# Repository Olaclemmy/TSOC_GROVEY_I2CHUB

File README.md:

# TSOC_GROVEY_I2CHUB
**TSOC_GROVEY_I2CHUB** is a four(4) port I2C Hub/Switch board, an Embedded Module for thingSoC.

The **TSOC_GROVEY_I2CHUB** can operate at either 3.3V or 5V, and can also level translate 3.3V processor I2C bus to 5V peripherals when needed.

The **TSOC_GROVEY_I2CHUB** allows you to connect [thingSoC](http://thingsoc.github.io/), [Mikrobus](http://www.mikroe.com/mikrobus/), 
and/or [Grove System](http://www.seeedstudio.com/blog/2016/03/09/tutorial-intro-to-grove-connectors-for-arduinoraspberry-pi-projects/) 
Modules all at the same time, with any processor module.
This gives you maximum flexiblity for sensor and actuator selection, and reuse. 

The thingSoC "Grovey Series" was designed as "Everyday Electronics", a no-frills, low cost, approach to modular embedded product design.
thingSoC boards are similar in size to most break-out-boards (BOBs), but feature a standardized stacking pinout, as well as an I2C metadata store (EEPROM)
to indicate what peripherals are installed.

[TSOC_GROVEY_I2CHUB](https://github.com/thingSoC/TSOC_GROVEY_I2CHUB/)

---------------------------------------

In this example, we use the [Grovey_I2CHUB](https://github.com/thingSoC/TSOC_GROVEY_I2CHUB) with the [Teensy3.x](https://www.pjrc.com/teensy/index.html) to support a Grove 16x2 LCD panel.
Since the Grove 16x2 LCD panel is a 5V peripheral, the [Grovey_I2CHUB](https://github.com/thingSoC/TSOC_GROVEY_I2CHUB) performs the voltage level translation
necessary to go from the 3.3V micro-processor to the 5V LCD controller. 

[TSOC_GROVEY_I2CHUB](https://github.com/thingSoC/TSOC_GROVEY_I2CHUB/)

* [thingSoC Compliant Module](http://www.thingsoc.com)
* [Mikrobus Compatible Module](http://www.mikroe.com/mikrobus/) 
* 5V Nominal Power Input
* 5V or 3.3V Operation
* Supports four (4) separate I2C busses 

---------------------------------------
## Example Uses

* Any time you want to connect four (4) of the same sensor, using the same I2C address, then you need an I2C Hub/Switch.
* Adds four (4) I2C ports to any [thingSoC](http://thingsoc.github.io/), [Mikrobus](http://www.mikroe.com/mikrobus/), 
and/or [Grove System](http://www.seeedstudio.com/blog/2016/03/09/tutorial-intro-to-grove-connectors-for-arduinoraspberry-pi-projects/) peripherals.

---------------------------------------
## 3D Model (Sketchup)

---------------------------------------
## Project Status

* 09/02/2016 : Revision 2.0 Release for PCB fab

## Revision 2.0 Notes: ##

* Add Ground Strap, remove FM24V10 FRAM, add GROVE I2C Slave connector slot.

## Revision 2.1 Notes: ##

* Remove Ground Strap, it was confusing for power configuration and assembly.
* Prototype testing complete, Production Ready

---------------------------------------

## Documentation Index <a name="documentation_index"/>

[Quick Start Guide](https://github.com/thingSoC/TSOC_GROVEY_I2CHUB/blob/master/TSOC_GROVEY_I2CHUB/docs/QuickStart.md)

[User Guide](https://github.com/thingSoC/TSOC_GROVEY_I2CHUB/blob/master/TSOC_GROVEY_I2CHUB/docs/UserGuide.md)

[Theory of Operation](https://github.com/thingSoC/TSOC_GROVEY_I2CHUB/blob/master/TSOC_GROVEY_I2CHUB/docs/TheoryOfOperation.md)

[thingSoC Organization Website](http://thingSoC.github.io)

[thingSoC FAQ - Frequently Asked Questions](http://thingsoc.github.io/support/faq.html)

---------------------------------------

[  
*thingSoC*](http://thingsoc.github.io)

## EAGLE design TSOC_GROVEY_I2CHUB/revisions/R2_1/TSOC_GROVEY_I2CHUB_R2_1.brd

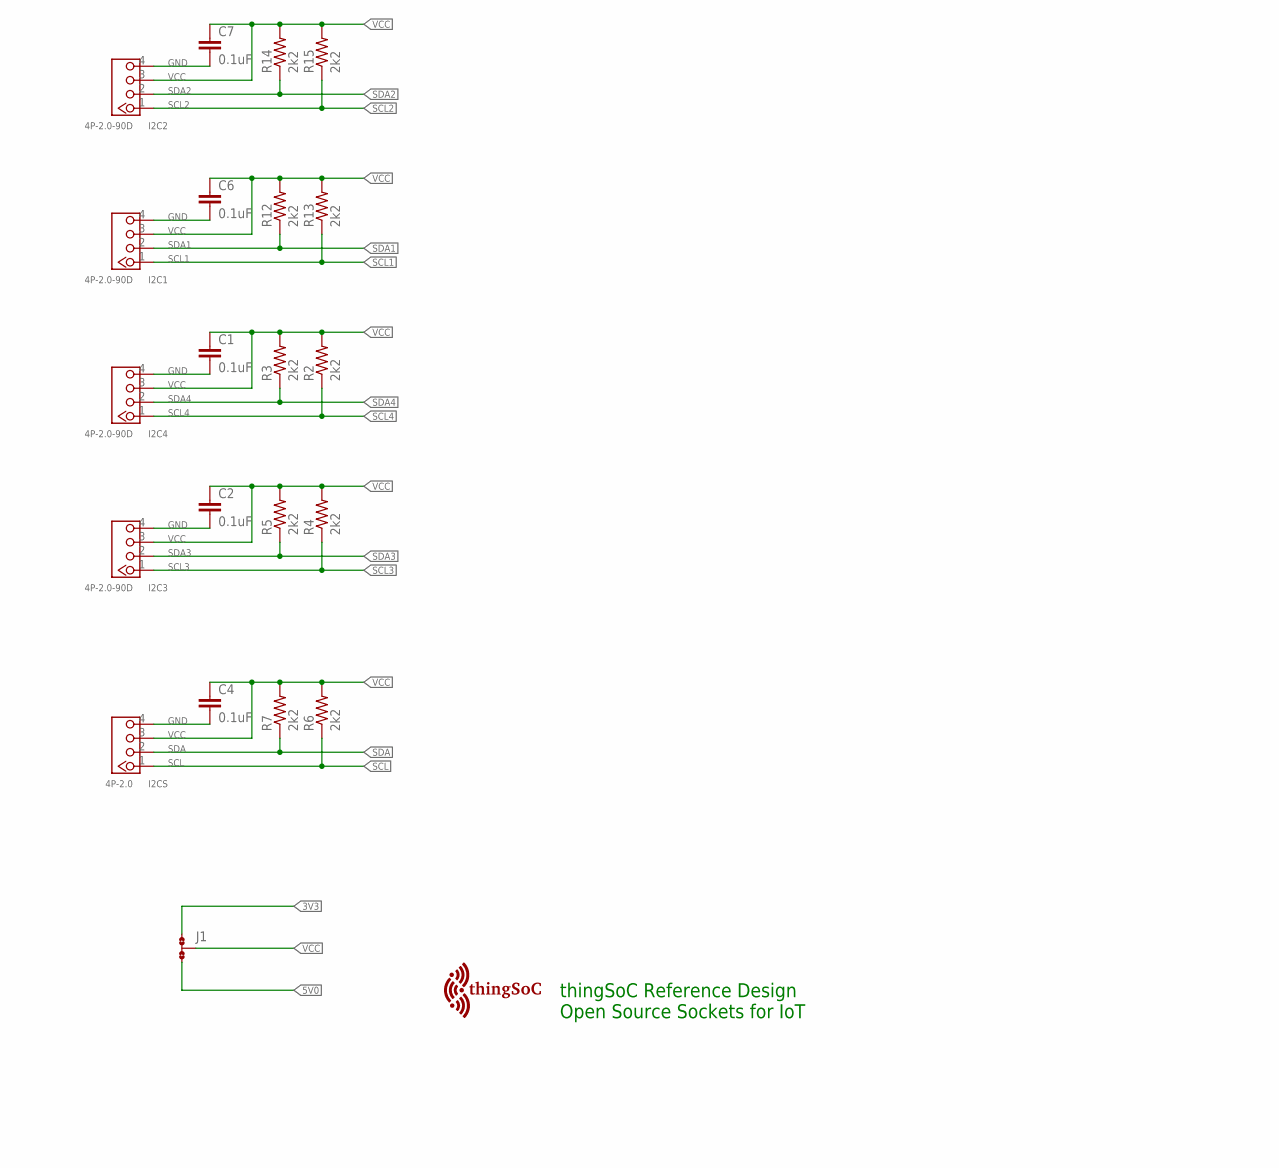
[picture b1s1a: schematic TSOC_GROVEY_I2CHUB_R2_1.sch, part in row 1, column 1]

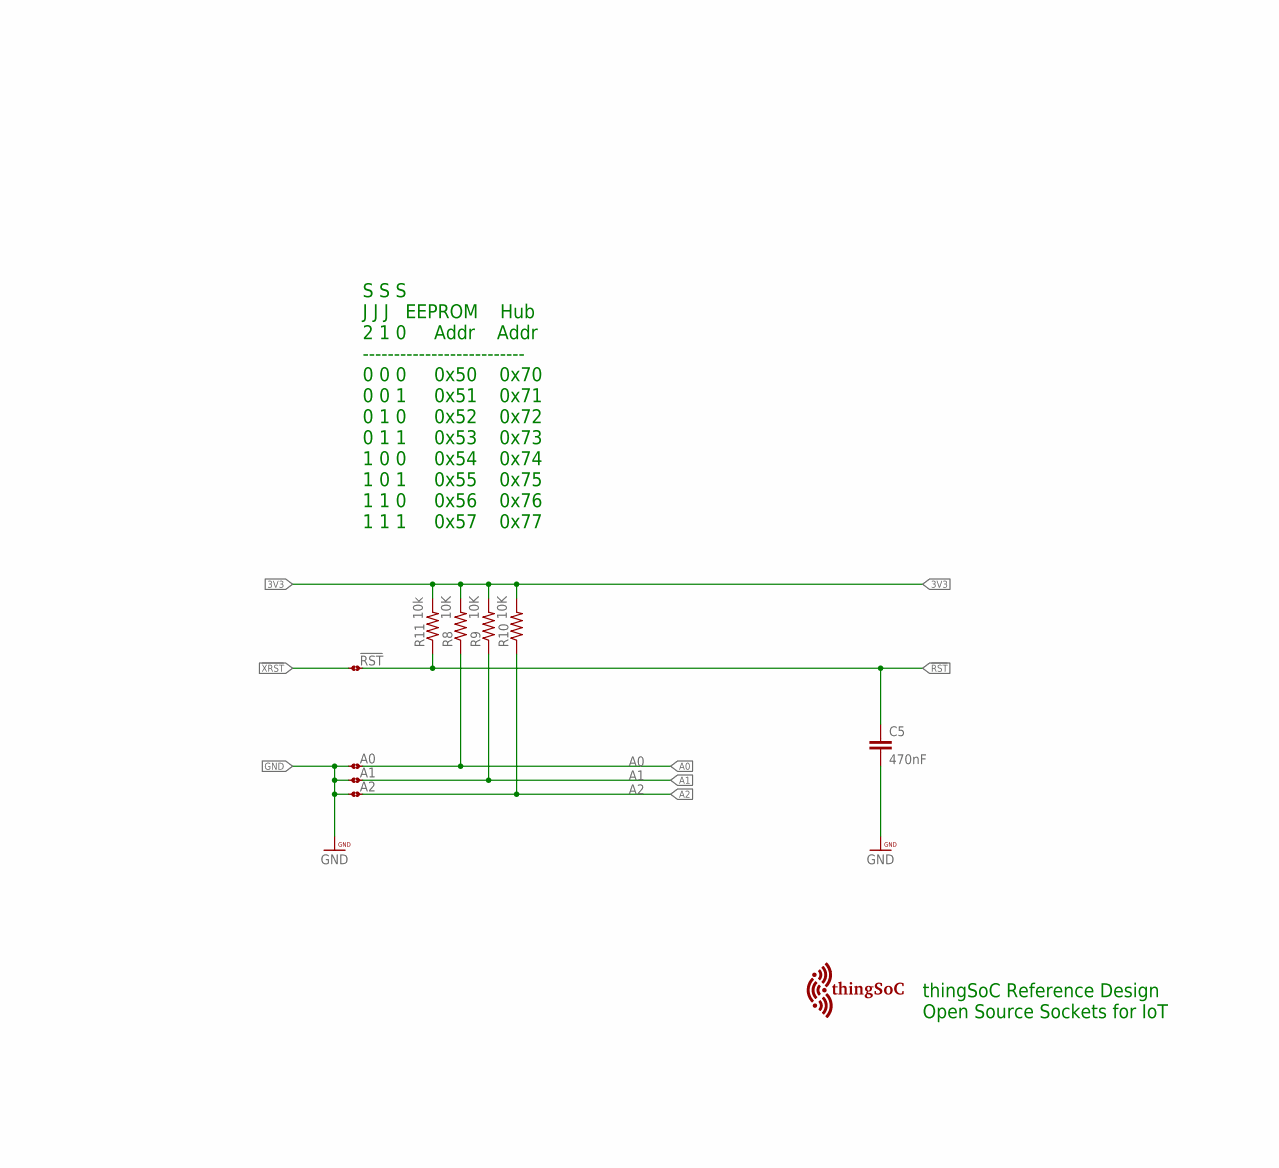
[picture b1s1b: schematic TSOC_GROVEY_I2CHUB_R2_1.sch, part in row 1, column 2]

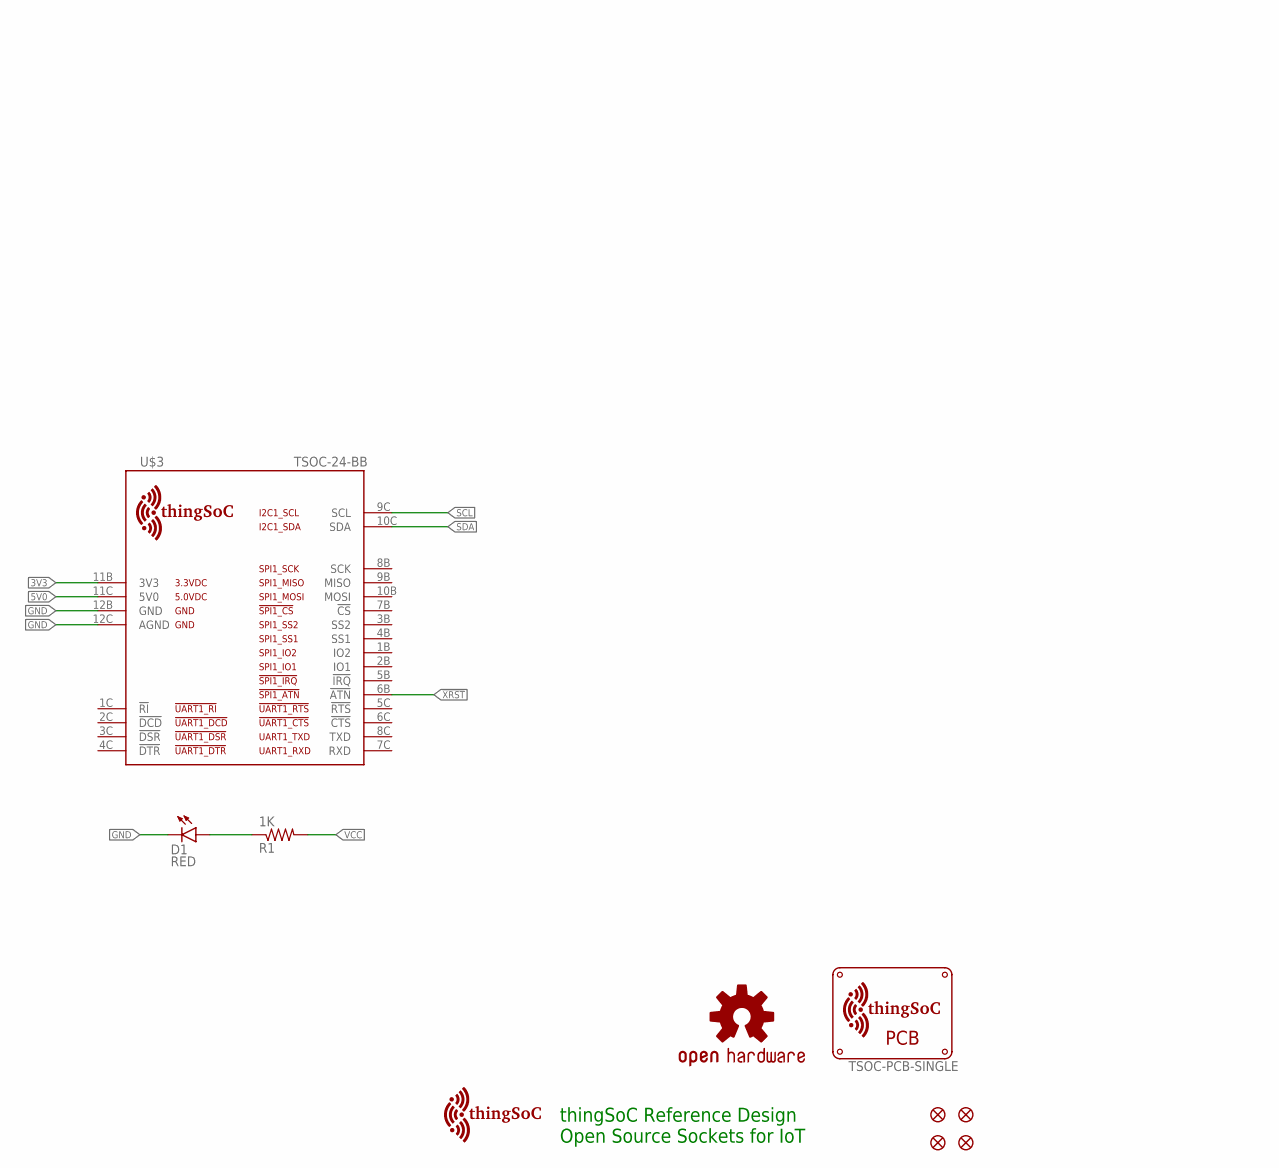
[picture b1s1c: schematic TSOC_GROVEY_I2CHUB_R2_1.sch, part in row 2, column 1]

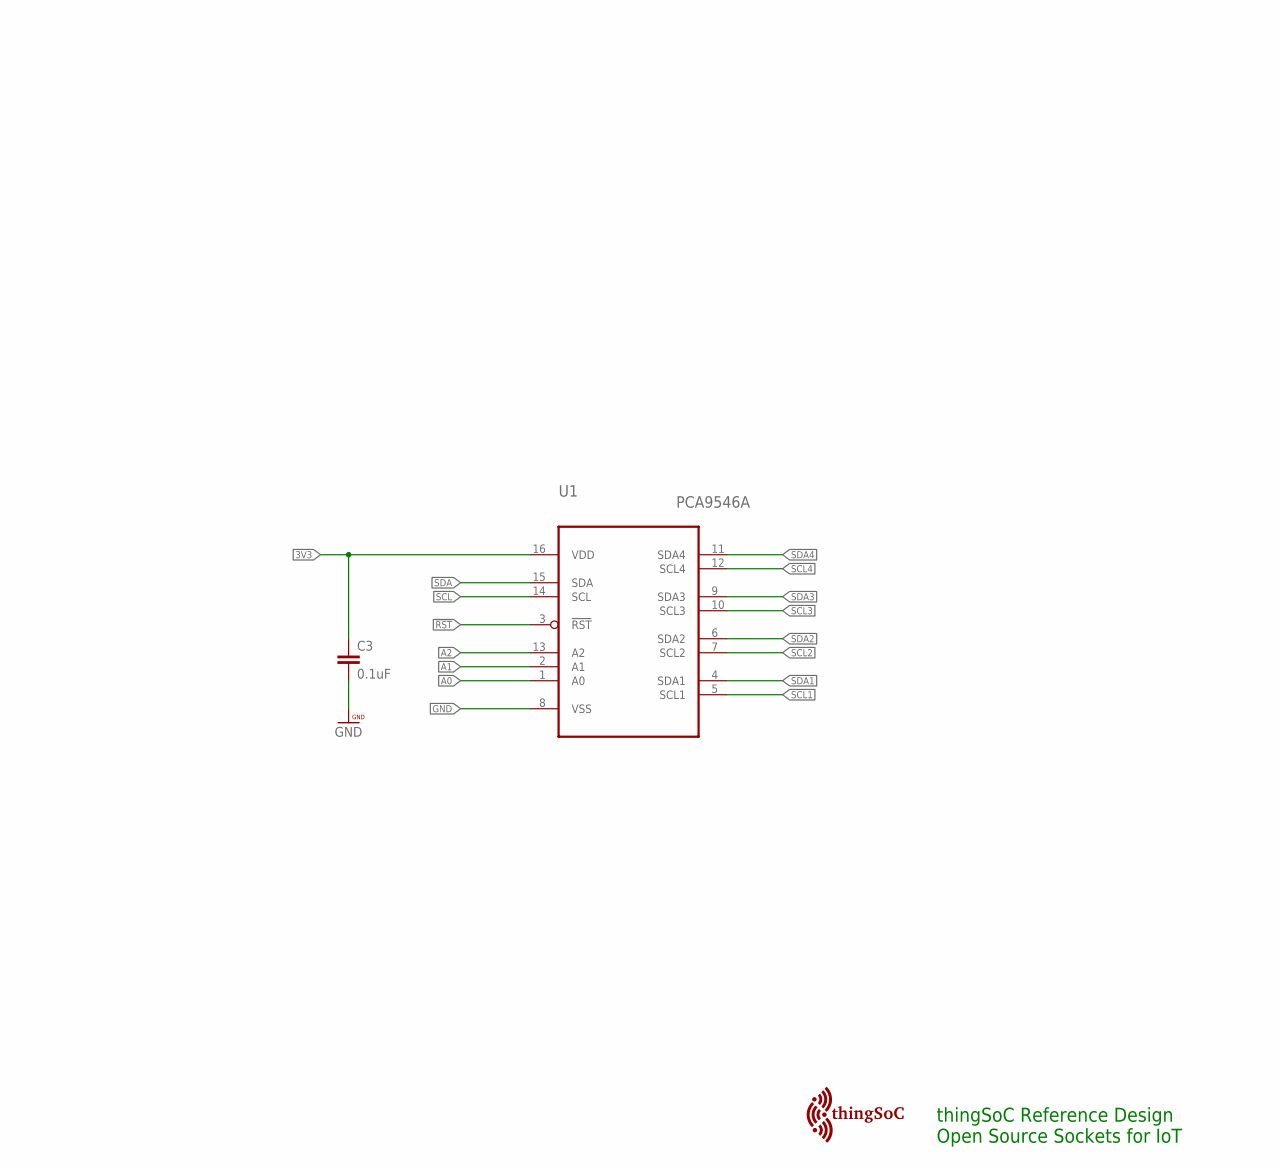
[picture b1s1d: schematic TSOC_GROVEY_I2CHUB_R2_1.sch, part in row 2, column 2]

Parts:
!RST: NO; JMP-2-NO
A0, A1, A2: NO; JMP-2-NO
C1, C2, C3, C4, C6, C7: 0.1uF; 0603-CAP
C5: 470nF; 0603-CAP
D1: RED; LED-0603
FID1, FID2, FID3, FID4: FIDUCIALUFIDUCIAL; MICRO-FIDUCIAL
I2C1, I2C2, I2C3, I2C4: 4P-2.0-90D; HW4-2.0-90D
I2CS: 4P-2.0; HW4-2.0
J1: NO; JMP-3-NO-PTH-2.54
LOGO1: OSHW-LOGOL; OSHW-LOGO-L
R1: 1K; 0603-RES
R2, R3, R4, R5, R6, R7, R12, R13, R14, R15: 2k2; 0603-RES
R8, R9, R10: 10K; 0603-RES
R11: 10k; 0603-RES
U1: PCA9546A; SOP65P640X110-16N
U$1, U$102, U$103: TSOC-LOGO-SMALL; TSOC-LOGO-SML
U$2: TSOC-PCB-SINGLE; TSOC-BB-BRD-DIM
U$3: TSOC-24-BB; TSOC-BB-S24
U$101: TSOC-LOGO-LRG

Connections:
3V3: C3.1, J1.1, R8.2, R9.2, R10.2, R11.2, U1.16 (VDD), U$3.11B (3V3)
5V0: J1.3, U$3.11C (5V0)
!RST: !RST.1, C5.1, R11.1, U1.3 (!RST)
!XRST: !RST.2, U$3.6B (!ATN)
A0: A0.2, R8.1, U1.1 (A0)
A1: A1.2, R9.1, U1.2 (A1)
A2: A2.2, R10.1, U1.13 (A2)
GND: A0.1, A1.1, A2.1, C1.2, C2.2, C3.2, C4.2, C5.2, C6.2, C7.2, D1.C, I2C1.4, I2C2.4, I2C3.4, I2C4.4, I2CS.4, U1.8 (VSS), U$3.12B (GND), U$3.12C (AGND)
unnamed: D1.A, R1.1
SCL: I2CS.1, R6.1, U1.14 (SCL), U$3.9C (SCL)
SCL1: I2C1.1, R13.1, U1.5 (SCL1)
SCL2: I2C2.1, R15.1, U1.7 (SCL2)
SCL3: I2C3.1, R4.1, U1.10 (SCL3)
SCL4: I2C4.1, R2.1, U1.12 (SCL4)
SDA: I2CS.2, R7.1, U1.15 (SDA), U$3.10C (SDA)
SDA1: I2C1.2, R12.1, U1.4 (SDA1)
SDA2: I2C2.2, R14.1, U1.6 (SDA2)
SDA3: I2C3.2, R5.1, U1.9 (SDA3)
SDA4: I2C4.2, R3.1, U1.11 (SDA4)
VCC: C1.1, C2.1, C4.1, C6.1, C7.1, I2C1.3, I2C2.3, I2C3.3, I2C4.3, I2CS.3, J1.2, R1.2, R2.2, R3.2, R4.2, R5.2, R6.2, R7.2, R12.2, R13.2, R14.2, R15.2

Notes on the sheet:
S S S J J J EEPROM Hub 2 1 0 Addr Addr -------------------------- 0 0 0 0x50 0x70 0 0 1 0x51 0x71 0 1 0 0x52 0x72 0 1 1 0x53 0x73 1 0 0 0x54 0x74 1 0 1 0x55 0x75 1 1 0 0x56 0x76 1 1 1 0x57 0x77
thingSoC Reference Design Open Source Sockets for IoT

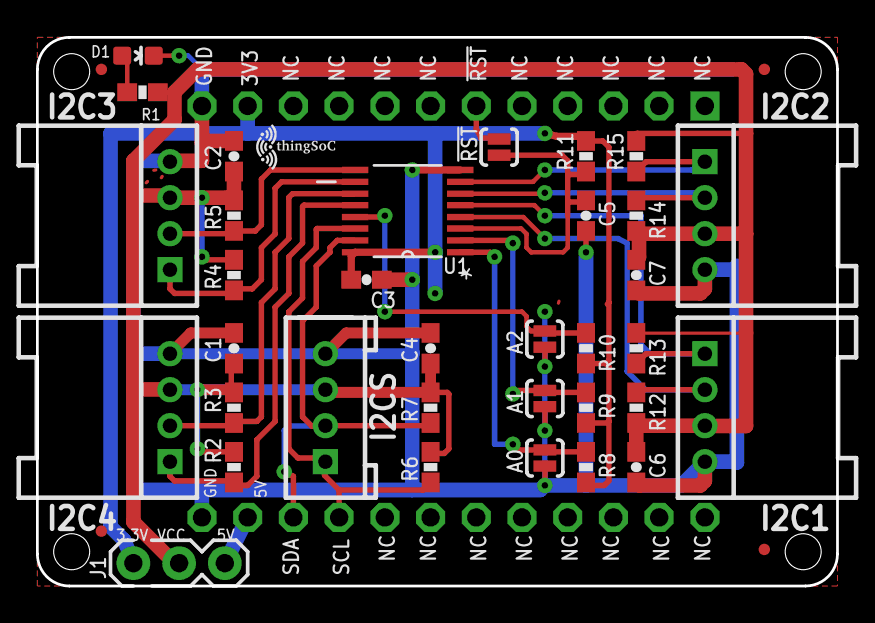
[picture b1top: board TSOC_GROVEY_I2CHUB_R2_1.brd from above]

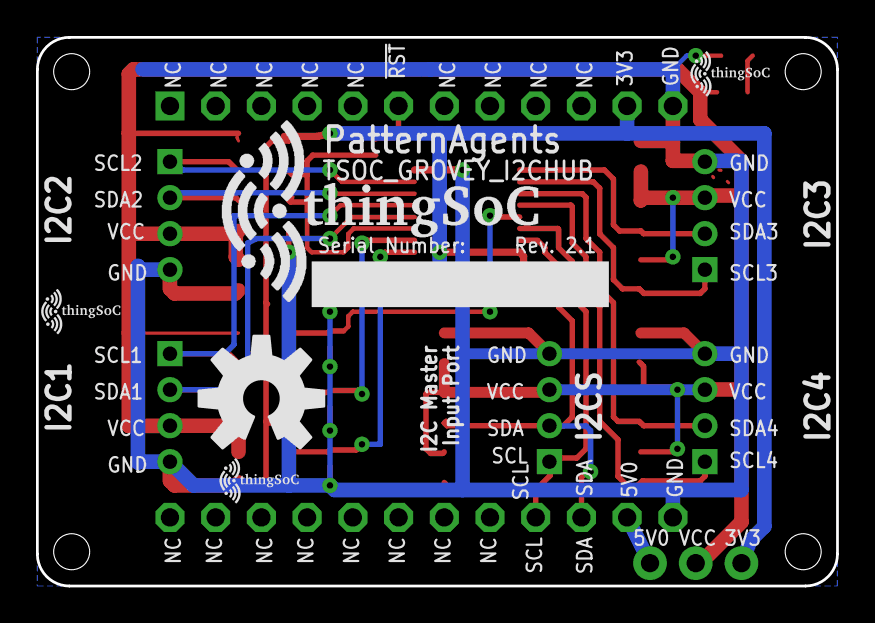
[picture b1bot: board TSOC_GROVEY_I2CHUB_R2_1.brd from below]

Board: 2 copper layers, 44.5 x 30.5 mm, 46 parts (5 on the bottom side), 20 nets.

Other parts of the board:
U$100: TSOC-LOGO-SMALL; TSOC-LOGO-SML

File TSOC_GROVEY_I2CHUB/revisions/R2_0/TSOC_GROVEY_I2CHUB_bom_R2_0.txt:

Partlist exported from U:/PatternAgents/eagle/TSOC_Modules/TSOC_GROVEY_I2CHUB/TSOC_GROVEY_I2CHUB/TSOC_GROVEY_I2CHUB.sch Revison 2.0 at 9/2/2016 12:30:56 PM

Part  Value             Device                          Package           Description                           
D1    RED               LED0603                         LED-0603          LEDs                                  
C1    0.1uF             CAP0603-CAP                     0603-CAP          Capacitor                             
C2    0.1uF             CAP0603-CAP                     0603-CAP          Capacitor                             
C3    0.1uF             CAP0603-CAP                     0603-CAP          Capacitor                             
C4    0.1uF             CAP0603-CAP                     0603-CAP          Capacitor                             
C5    470pF             CAP0603-CAP                     0603-CAP          Capacitor                             
C6    0.1uF             CAP0603-CAP                     0603-CAP          Capacitor                             
C7    0.1uF             CAP0603-CAP                     0603-CAP          Capacitor                             
I2C1  4P-2.0-90D        GROVE-CONNECTOR-DIP-90D(4P-2.0) HW4-2.0-90D       320110034                             
I2C2  4P-2.0-90D        GROVE-CONNECTOR-DIP-90D(4P-2.0) HW4-2.0-90D       320110034                             
I2C3  4P-2.0-90D        GROVE-CONNECTOR-DIP-90D(4P-2.0) HW4-2.0-90D       320110034                             
I2C4  4P-2.0-90D        GROVE-CONNECTOR-DIP-90D(4P-2.0) HW4-2.0-90D       320110034                             
R1    1K                RESISTOR_SFE0603-RES            0603-RES          Resistor                              
R2    2k2               RESISTOR0603-RES                0603-RES          Resistor                              
R3    2k2               RESISTOR0603-RES                0603-RES          Resistor                              
R4    2k2               RESISTOR0603-RES                0603-RES          Resistor                              
R5    2k2               RESISTOR0603-RES                0603-RES          Resistor                              
R6    2k2               RESISTOR0603-RES                0603-RES          Resistor                              
R7    2k2               RESISTOR0603-RES                0603-RES          Resistor                              
R8    10K               RESISTOR0603-RES                0603-RES          Resistor                              
R9    10K               RESISTOR0603-RES                0603-RES          Resistor                              
R10   10K               RESISTOR0603-RES                0603-RES          Resistor                              
R11   10k               RESISTOR0603-RES                0603-RES          Resistor                              
R12   2k2               RESISTOR0603-RES                0603-RES          Resistor                              
R13   2k2               RESISTOR0603-RES                0603-RES          Resistor                              
R14   2k2               RESISTOR0603-RES                0603-RES          Resistor                              
R15   2k2               RESISTOR0603-RES                0603-RES          Resistor                              
U1    PCA9546A          PCA9546A                        SOP65P640X110-16N 4-channel I2C-bus switch with reset   
J1    NO                JMP-3-NO-PTH                    JMP-3-NO-PTH-2.54 Three Terminal Jumper
JMP1  Jumper            2 Pin Jumper                    2 Pin Jumper      Installed on J1-1 to J1-2 (3.3V)

Do Not Populate
--------------------------------------------------------------------------------------------
GND                     M01PTH                          1X01              Ground Strap  
I2CS  4P-2.0            GROVE-CONNECTOR-DIP(4P-2.0)     HW4-2.0           320110033                             
!RST  NO                JMP-2-NO                        JMP-2-NO          Basic Jumper - Normally Open          
A0    NO                JMP-2-NO                        JMP-2-NO          Basic Jumper - Normally Open          
A1    NO                JMP-2-NO                        JMP-2-NO          Basic Jumper - Normally Open          
A2    NO                JMP-2-NO                        JMP-2-NO          Basic Jumper - Normally Open

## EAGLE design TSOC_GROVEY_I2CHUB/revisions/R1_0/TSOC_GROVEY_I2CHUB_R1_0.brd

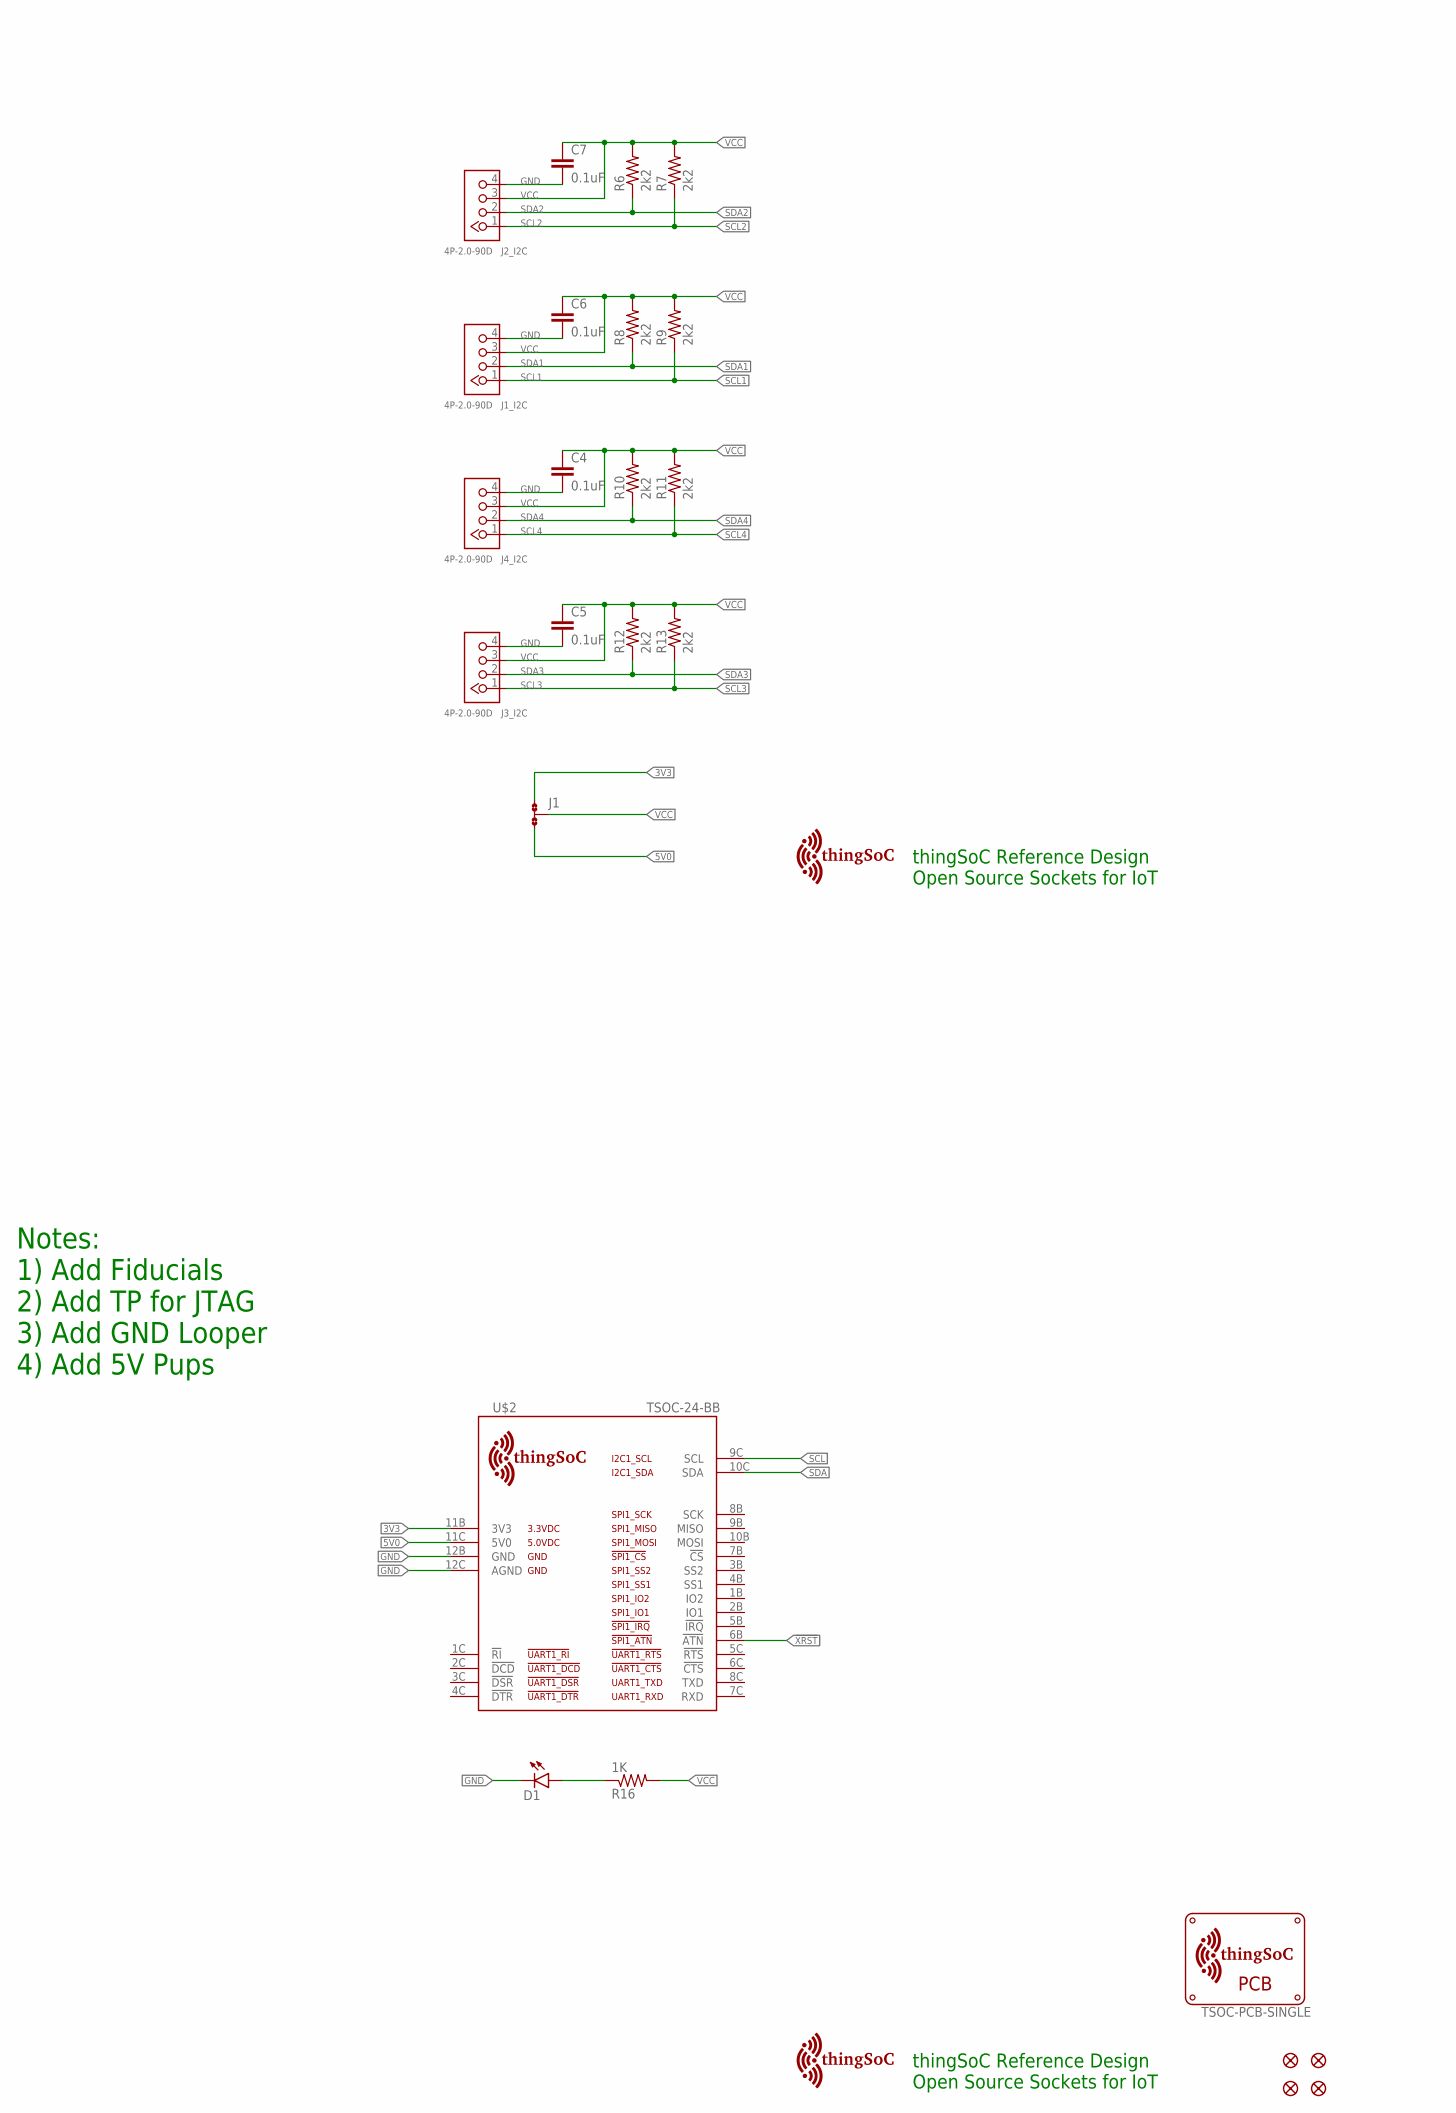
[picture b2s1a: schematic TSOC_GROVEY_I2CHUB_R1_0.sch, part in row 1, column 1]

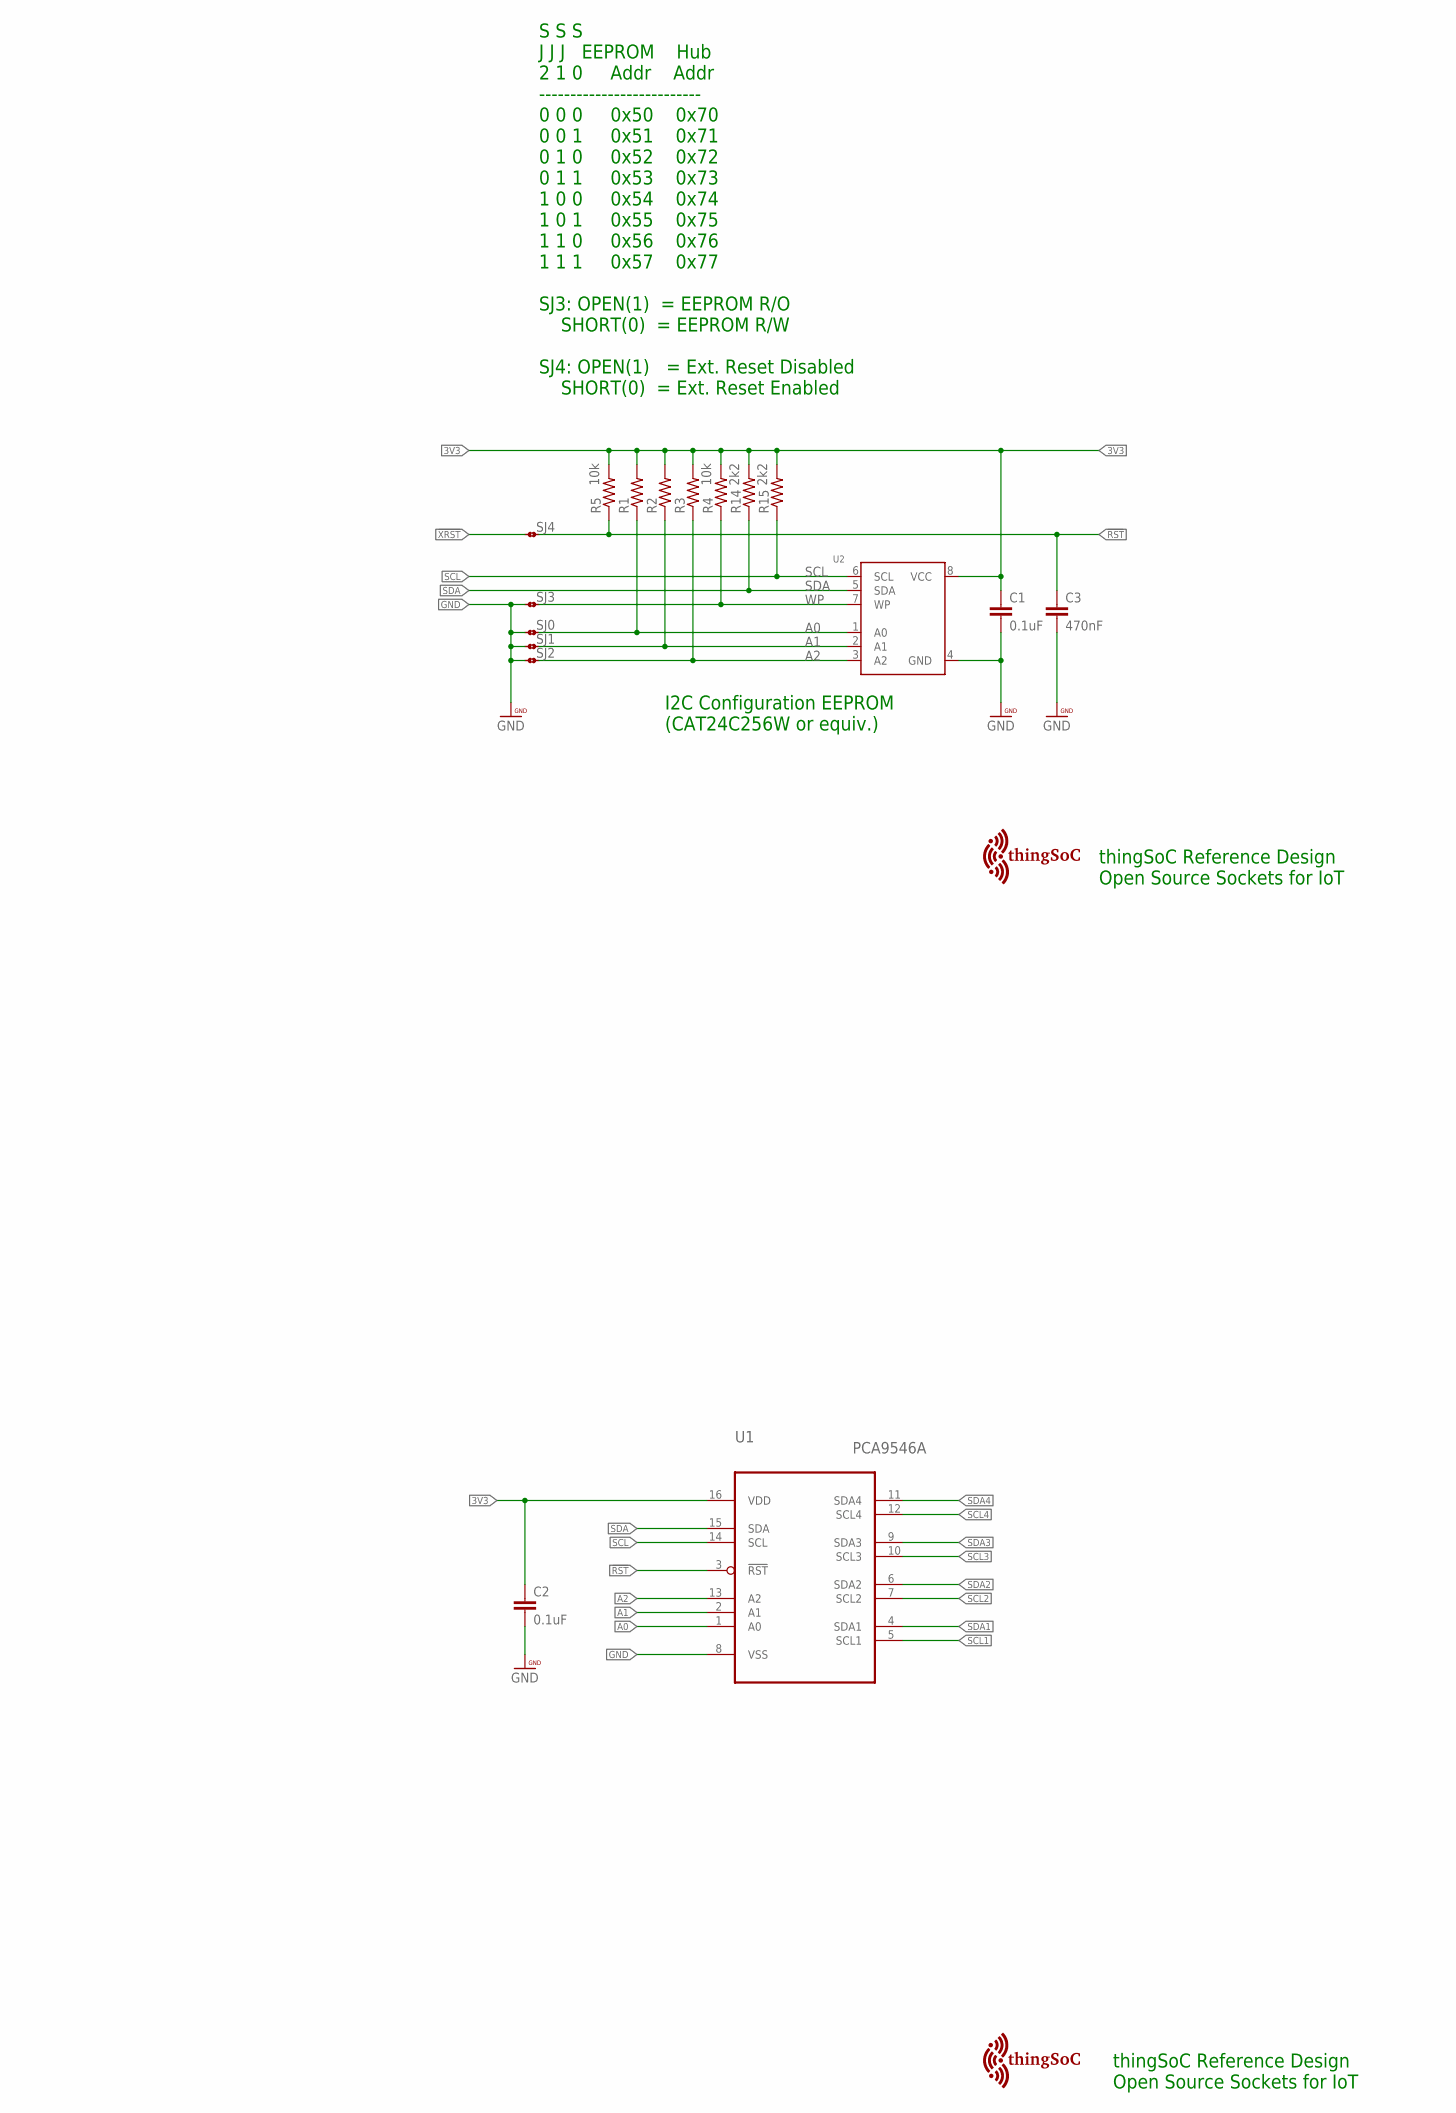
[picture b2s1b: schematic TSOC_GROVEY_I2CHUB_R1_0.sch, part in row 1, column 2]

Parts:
C1, C2, C4, C5, C6, C7: 0.1uF; 0603-CAP
C3: 470nF; 0603-CAP
D1: LED0603; LED-0603
FID1, FID2, FID3, FID4: FIDUCIALUFIDUCIAL; MICRO-FIDUCIAL
J1: JMP-3-NO-PTH; JMP-3-NO-PTH-2.54
J1_I2C, J2_I2C, J3_I2C, J4_I2C: 4P-2.0-90D; HW4-2.0-90D
R1, R2, R3: RESISTOR0603-RES; 0603-RES
R4, R5: 10k; 0603-RES
R6, R7, R8, R9, R10, R11, R12, R13, R14, R15: 2k2; 0603-RES
R16: 1K; 0603-RES
SJ0, SJ1, SJ2, SJ3, SJ4: JMP-2-NO
U1: PCA9546A; SOP65P640X110-16N
U2: EEPROM_I2C_SOIC8_GENERIC; SOIC8_150MIL
U$1: TSOC-PCB-SINGLE; TSOC-BB-BRD-DIM
U$2: TSOC-24-BB; TSOC-BB-S24
U$7, U$9, U$100: TSOC-LOGO-SMALL; TSOC-LOGO-SML
U$101: TSOC-LOGO-LRG

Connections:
3V3: C1.1, C2.1, J1.1, R1.2, R2.2, R3.2, R4.2, R5.2, R14.2, R15.2, U1.16 (VDD), U2.8 (VCC), U$2.11B (3V3)
5V0: J1.3, U$2.11C (5V0)
!RST: C3.1, R5.1, SJ4.1, U1.3 (!RST)
!XRST: SJ4.2, U$2.6B (!ATN)
A0: R1.1, SJ0.2, U1.1 (A0), U2.1 (A0)
A1: R2.1, SJ1.2, U1.2 (A1), U2.2 (A1)
A2: R3.1, SJ2.2, U1.13 (A2), U2.3 (A2)
GND: C1.2, C2.2, C3.2, C4.2, C5.2, C6.2, C7.2, D1.C, J1_I2C.4, J2_I2C.4, J3_I2C.4, J4_I2C.4, SJ0.1, SJ1.1, SJ2.1, SJ3.1, U1.8 (VSS), U2.4 (GND), U$2.12B (GND), U$2.12C (AGND)
unnamed: D1.A, R16.1
SCL: R15.1, U1.14 (SCL), U2.6 (SCL), U$2.9C (SCL)
SCL1: J1_I2C.1, R9.1, U1.5 (SCL1)
SCL2: J2_I2C.1, R7.1, U1.7 (SCL2)
SCL3: J3_I2C.1, R13.1, U1.10 (SCL3)
SCL4: J4_I2C.1, R11.1, U1.12 (SCL4)
SDA: R14.1, U1.15 (SDA), U2.5 (SDA), U$2.10C (SDA)
SDA1: J1_I2C.2, R8.1, U1.4 (SDA1)
SDA2: J2_I2C.2, R6.1, U1.6 (SDA2)
SDA3: J3_I2C.2, R12.1, U1.9 (SDA3)
SDA4: J4_I2C.2, R10.1, U1.11 (SDA4)
VCC: C4.1, C5.1, C6.1, C7.1, J1.2, J1_I2C.3, J2_I2C.3, J3_I2C.3, J4_I2C.3, R6.2, R7.2, R8.2, R9.2, R10.2, R11.2, R12.2, R13.2, R16.2
WP: R4.1, SJ3.2, U2.7 (WP)

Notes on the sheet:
Notes: 1) Add Fiducials 2) Add TP for JTAG 3) Add GND Looper 4) Add 5V Pups
I2C Configuration EEPROM (CAT24C256W or equiv.)
S S S J J J EEPROM Hub 2 1 0 Addr Addr -------------------------- 0 0 0 0x50 0x70 0 0 1 0x51 0x71 0 1 0 0x52 0x72 0 1 1 0x53 0x73 1 0 0 0x54 0x74 1 0 1 0x55 0x75 1 1 0 0x56 0x76 1 1 1 0x57 0x77 SJ3: OPEN(1) = EEPROM R/O SHORT(0) = EEPROM R/W SJ4: OPEN(1) = Ext. Reset Disabled SHORT(0) = Ext. Reset 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
thingSoC Reference Design Open Source Sockets for IoT

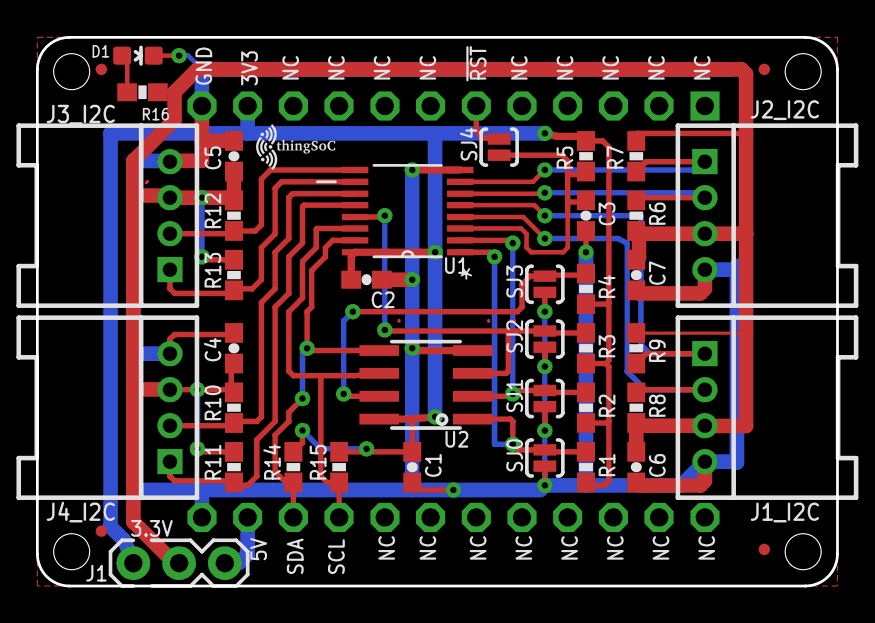
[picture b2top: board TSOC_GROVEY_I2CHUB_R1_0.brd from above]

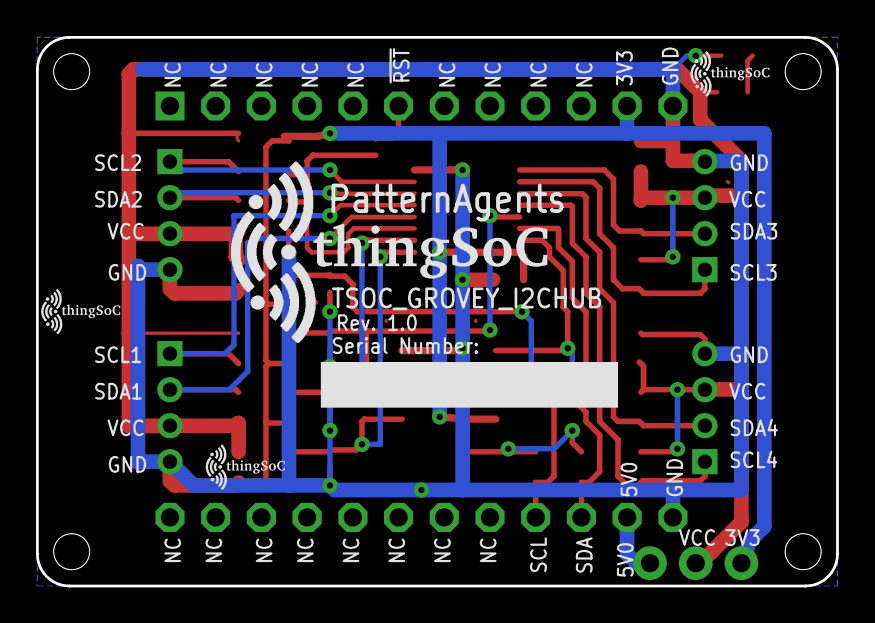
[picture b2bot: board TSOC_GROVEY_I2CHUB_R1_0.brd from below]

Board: 2 copper layers, 44.5 x 30.5 mm, 47 parts (4 on the bottom side), 21 nets.

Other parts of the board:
U$8: TSOC-LOGO-SMALL; TSOC-LOGO-SML

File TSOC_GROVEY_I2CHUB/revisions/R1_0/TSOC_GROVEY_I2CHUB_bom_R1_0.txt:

Partlist exported from U:/PatternAgents/eagle/TSOC_Modules/TSOC_GROVEY_I2CHUB/TSOC_GROVEY_I2CHUB/TSOC_GROVEY_I2CHUB.sch at 8/26/2016 2:21:03 PM

Qty Value             Device                          Package           Parts                                        Description
1                     EEPROM_I2C_SOIC8_GENERIC        SOIC8_150MIL      U2                                           Note: The same pinout is used 
5                     JMP-2-NO                        JMP-2-NO          SJ0, SJ1, SJ2, SJ3, SJ4                      Basic Jumper - Normally Open
1                     JMP-3-NO-PTH                    JMP-3-NO-PTH-2.54 J1                                           Three Terminal Jumper - Normally Op
1                     LED0603                         LED-0603          D1                                           LEDs
3                     RESISTOR0603-RES                0603-RES          R1, R2, R3                                   Resistor  
6   0.1uF             CAP0603-CAP                     0603-CAP          C1, C2, C4, C5, C6, C7                       Capacitor     
2   10k               RESISTOR0603-RES                0603-RES          R4, R5                                       Resistor
1   1K                RESISTOR_SFE0603-RES            0603-RES          R16                                          Resistor          
10  2k2               RESISTOR0603-RES                0603-RES          R6, R7, R8, R9, R10, R11, R12, R13, R14, R15 Resistor    
1   470nF             CAP0603-CAP                     0603-CAP          C3                                           Capacitor 
4   4P-2.0-90D        GROVE-CONNECTOR-DIP-90D(4P-2.0) HW4-2.0-90D       J1_I2C, J2_I2C, J3_I2C, J4_I2C               320110034                          
1   PCA9546A          PCA9546A                        SOP65P640X110-16N U1                                           4-channel I2C-bus switch with reset

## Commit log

2016-09-02 initial version
2016-09-04 add product images
2016-09-04 update documentation
2016-10-17 update BOM
2017-01-16 update documetation

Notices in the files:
parts and their libraries:
thingSoC: License : http://creativecommons.org/licenses/by-sa/4.0
(Creative Commons 4.0)
PatternAgents-NXP: License : http://creativecommons.org/licenses/by-sa/3.0
(Creative Commons 3.0)
SparkFun-Passives: Licensing: CC v3.0 Share-Alike You are welcome to use this library for commercial purposes.
